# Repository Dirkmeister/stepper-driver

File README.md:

# Universal Stepper Tester

A bench tool for NEMA 17 and smaller bipolar stepper motors: plug a motor in, spin it, set current and microstepping, and read the driver's own diagnostics on an OLED. Every power-up runs a self test that names the failing part of the board. By -DK.

| | |
|---|---|
| MCU | ATmega328P (DIP-28, socketed), 16 MHz crystal, ISP-programmed, no bootloader |
| Driver | BigTreeTech TMC2209 V1.2 StepStick, single-wire UART, up to about 1.75 A RMS |
| UI | 0.96 in SSD1306 I2C OLED, EC11 encoder with push, on a separate front board |
| Power | 12 V brick, inline 2 A blade fuse, panel switch, reverse-polarity FET, L7805 |
| Boards | Rev A: main 100.6 x 89.0 mm + front 70.0 x 38.1 mm, 2 layers, one JLCPCB panel |
| Firmware | v1.0 (2026-10-12), no libraries, verified in a board simulator (sizes in `CLAUDE.md`) |

## Status

Rev A boards are built and the first one powers up; the motor only vibrates so far, and the real-hardware self test still has to be recorded. Details and open issues: **[STATUS.md](STATUS.md)**.

## Repository

| Path | What |
|---|---|
| [`STATUS.md`](STATUS.md) | current state, active thread, queue, open items |
| [`CHANGELOG.md`](CHANGELOG.md) | history |
| [`CLAUDE.md`](CLAUDE.md) | rules and session protocol for working on this with Claude |
| [`docs/hardware.md`](docs/hardware.md) | design reference: power path, pin map, connectors, BOM, layout rules, display options |
| [`docs/errata-rev-a.md`](docs/errata-rev-a.md) | known Rev A problems, workarounds, Rev B candidates |
| [`docs/assembly.md`](docs/assembly.md) | build order, first power-up, harnesses, ribbon, motor wiring |
| [`docs/firmware.md`](docs/firmware.md) | self test, controls, menu, faults, debug log, backlog |
| [`docs/build-and-flash.md`](docs/build-and-flash.md) | MiniCore, Uno as ISP, fuses, expected warnings |
| [`docs/decisions.md`](docs/decisions.md) | why the design is the way it is |
| [`docs/inventory.md`](docs/inventory.md) | parts the owner has stated outside his inventory file, and the buy list (the inventory file itself is in the claude.ai Project knowledge) |
| [`docs/history/`](docs/history/) | sources, the 2026-10-06 progress doc |
| [`docs/claude-project-instructions.md`](docs/claude-project-instructions.md) | text for the claude.ai Project's instructions field |
| [`docs/seeds.md`](docs/seeds.md) | opening message for the next thread |
| [`firmware/`](firmware/) | `stepper_tester/` (the board firmware), `bringup/` (old Uno breadboard sketches) |
| [`tools/`](tools/) | `build.sh` headless build, `sim/` board simulator with fault scenarios |
| [`hardware/`](hardware/) | Rev A KiCad project and production files, as ordered |

## Flash the firmware (short version)

1. Arduino IDE: add the MiniCore URL in Preferences, install **MiniCore** from Boards Manager.
2. Upload ArduinoISP to an Uno, then 10 uF from its RESET to GND.
3. Tools: MiniCore ATmega328, External 16 MHz, BOD 2.7V, EEPROM retained, LTO enabled, 328P / 328PA, No bootloader, Programmer "Arduino as ISP".
4. Wire the Uno to the chip (breadboard jig or J2), Burn Bootloader once per chip, then Sketch > Upload Using Programmer.

Full procedure and what the warnings mean: [`docs/build-and-flash.md`](docs/build-and-flash.md).

## Safety

- Never plug or unplug a motor with 12 V on.
- J1 pin 1 is **negative**.
- J3 (ISP PWR) off whenever the brick is plugged in.
- Keep the input at 9 to 14 V while the 15 V zener (D1) is fitted.

## Working on it

The repo is the source of truth. Work in small commits (`fw:`, `hw:`, `docs:`, `tools:`), keep `STATUS.md` current, tag firmware releases `fw-vX.Y` and ordered boards `hw-rev-X`. Firmware changes must pass `tools/build.sh` and `tools/sim/run_all.sh` before they go on a chip. Details in [`CLAUDE.md`](CLAUDE.md).

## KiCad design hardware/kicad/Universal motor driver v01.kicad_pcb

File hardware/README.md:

# Hardware design files

Rev A as ordered from JLCPCB, copied byte-for-byte from the owner's PC on 2026-11-25. Tag `hw-rev-a` marks the commit that added them. Where these files and `docs/hardware.md` (compiled from the design chats) disagree, the files win.

## What's here

| Path | What | Notes |
|---|---|---|
| `kicad/Universal motor driver v01.kicad_pro` | KiCad project | the project name has spaces |
| `kicad/Universal motor driver v01.kicad_sch` | root schematic, the only sheet | title block: Universal Stepper Tester, rev A, 2026-10-05 |
| `kicad/Universal motor driver v01.kicad_pcb` | the board as ordered | same file as KiCad's 2026-10-06 02:15 backup, saved between the two gerber exports below, which are identical |
| `kicad/stepper_tester.kicad_sym` | project symbol library | holds `BTT_TMC2209_V1.2` |
| `kicad/sym-lib-table` | project symbol library table | see Known issues |
| `production/rev-A/` | fab outputs from 2026-10-06 | see below |

## Production files (Rev A)

| File | Exported (2026-10-06, CDT) | Notes |
|---|---|---|
| `Universal_motor_driver_v01.zip` | 02:19 | gerbers and drills, the file JLC needs |
| `bom.csv`, `positions.csv`, `designators.csv`, `netlist.ipc` | 02:19 | same export; LCSC part numbers blank |
| `production.zip` | 02:13 | an earlier export of the same set |

Which zip was uploaded isn't recorded, and it doesn't matter: the two exports' gerbers and drills match line for line apart from the creation time. Both carry the two known export problems: the encoder slots are routed slots, not the G85 mode JLC asks for (errata E5), and the silkscreen has lines down to 0.064 mm (E6). A G85 drill file was exported at 02:18 but never went into a zip.

`.gitattributes` stores everything under `production/` exactly as exported (the csv and ipc files are CRLF).

## Known issues in these files

- `sym-lib-table` maps the `tmc2209 module` library to the project folder by an absolute path on the owner's PC, not to `stepper_tester.kicad_sym`, so it won't resolve in a clone. The schematic keeps its own copy of every symbol, so it opens anyway. For Rev B, point it at `${KIPRJMOD}/stepper_tester.kicad_sym`.
- Not committed, still on the owner's PC: KiCad backups, `.kicad_prl` (local window state), 7 older or unused `.kicad_sch` files, the loose 02:18 drill files and the `.csv` / `.xlsx` spreadsheets in the project folder.

## Revisions

| Rev | Date | Status | Notes |
|---|---|---|---|
| A | ordered by 2026-10-06, delivered 2026-10-12 | built, under test | errata in `docs/errata-rev-a.md` |
| B | | not started | candidate changes at the end of the errata doc |

From Rev B on: work on a branch (`hw/rev-b`), keep the KiCad project name, bump the silkscreen revision text, and tag `hw-rev-b` at the commit that gets ordered. Dallas creates tags (GitHub Releases or git on the PC): tag pushes from Claude sessions are refused.

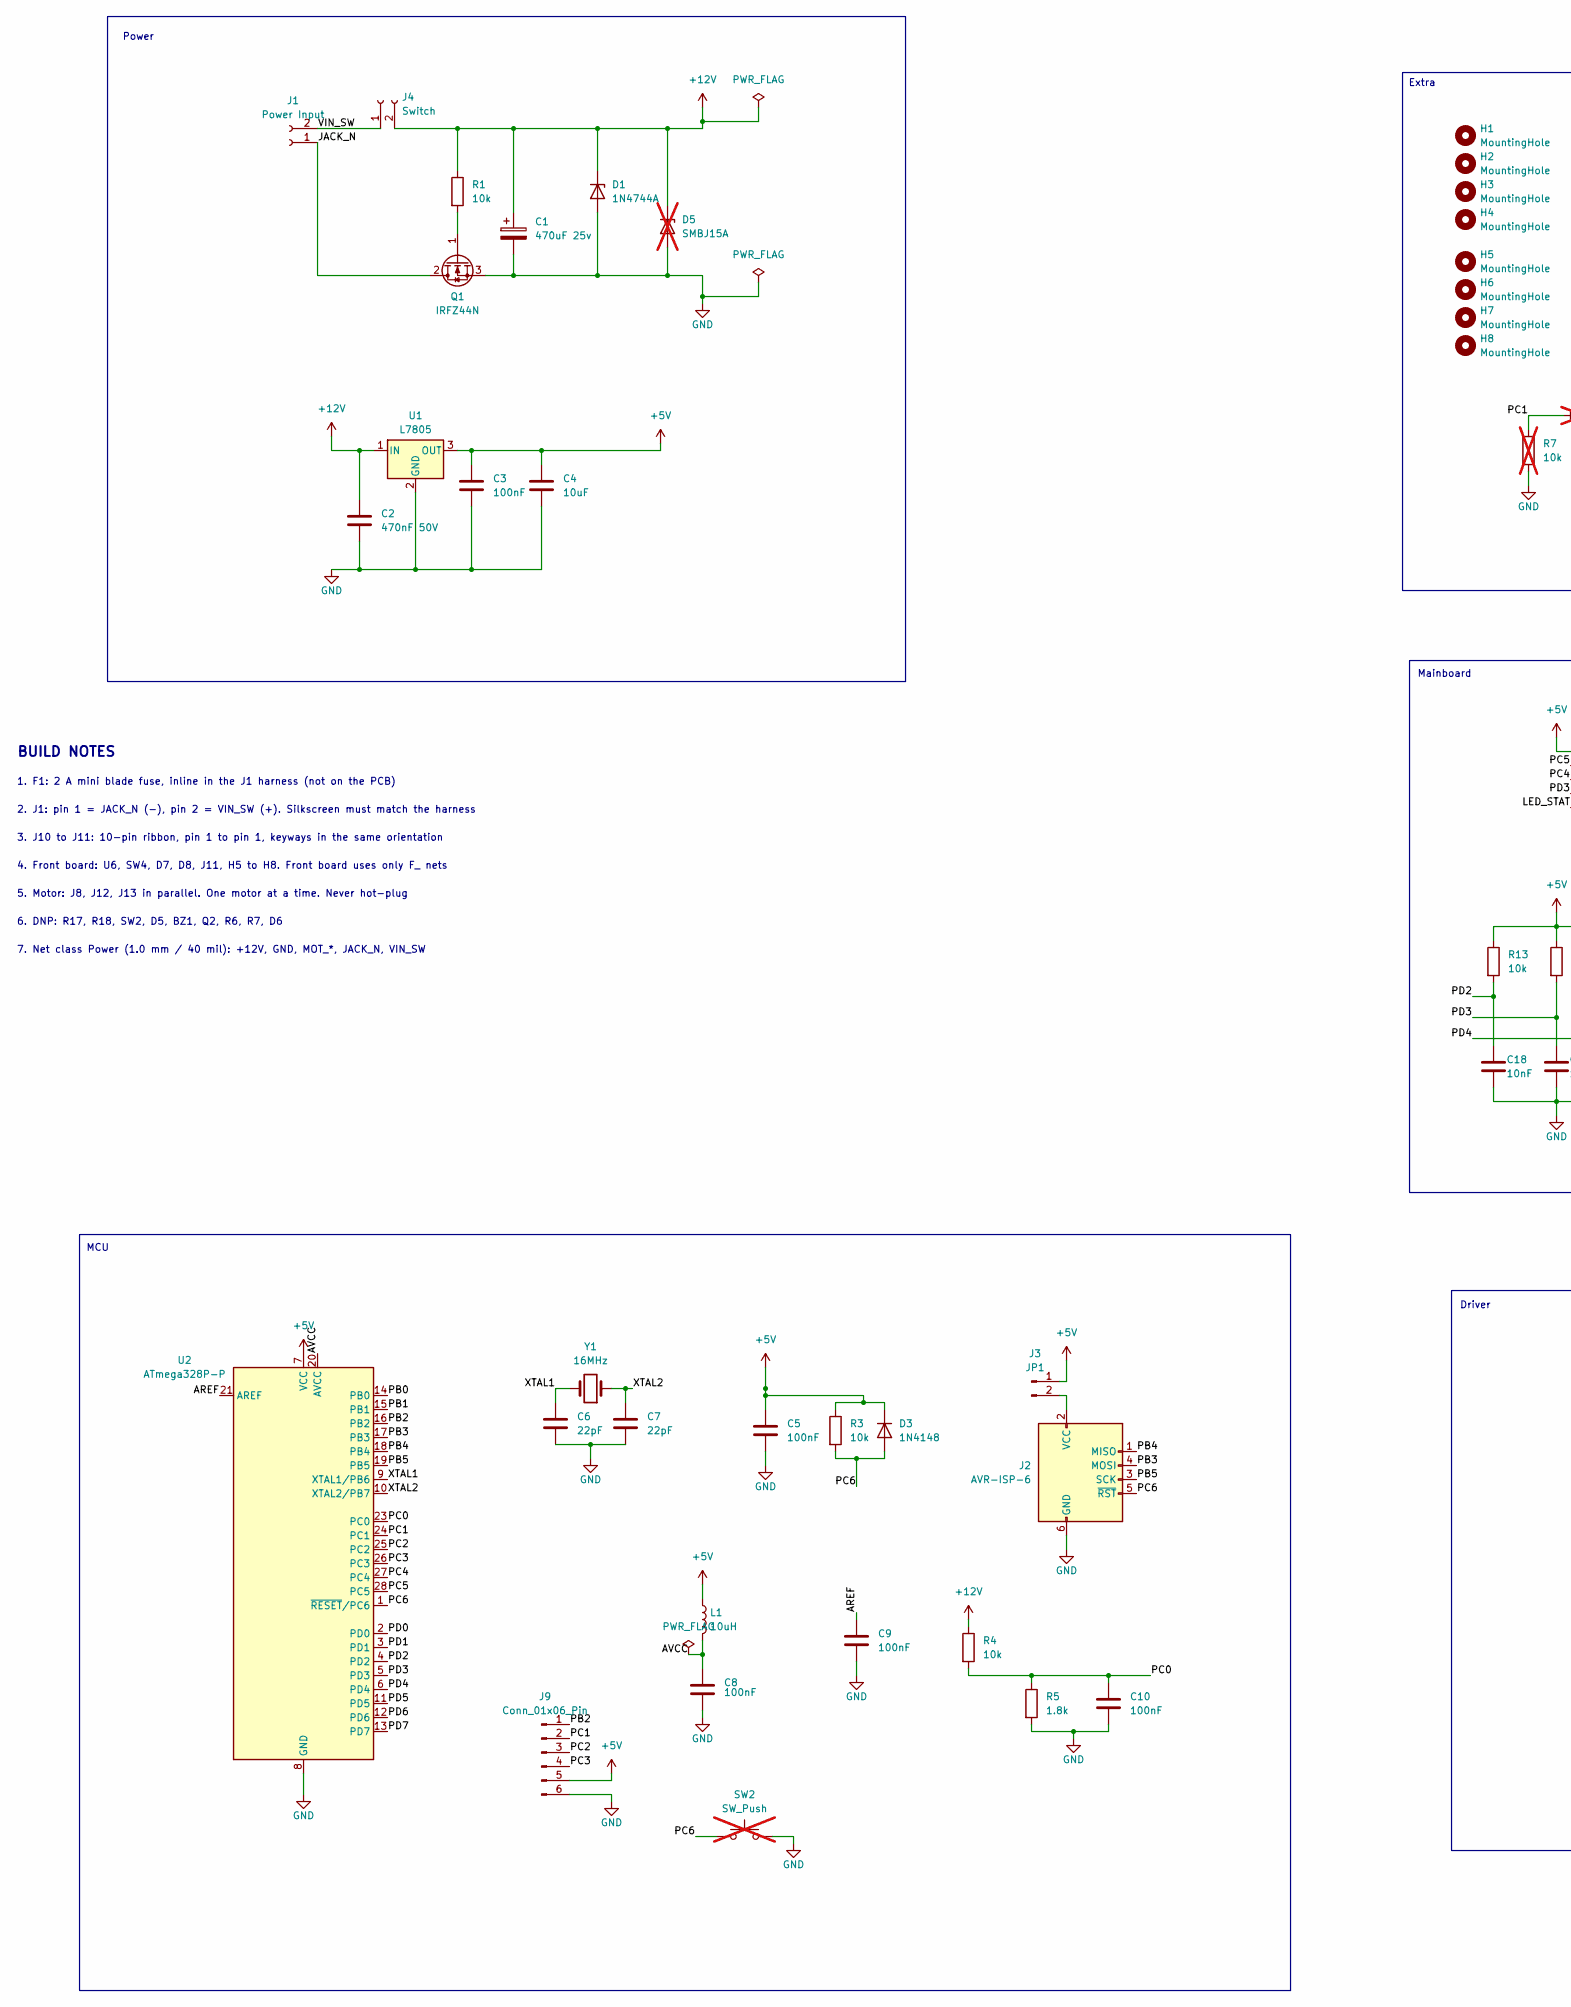
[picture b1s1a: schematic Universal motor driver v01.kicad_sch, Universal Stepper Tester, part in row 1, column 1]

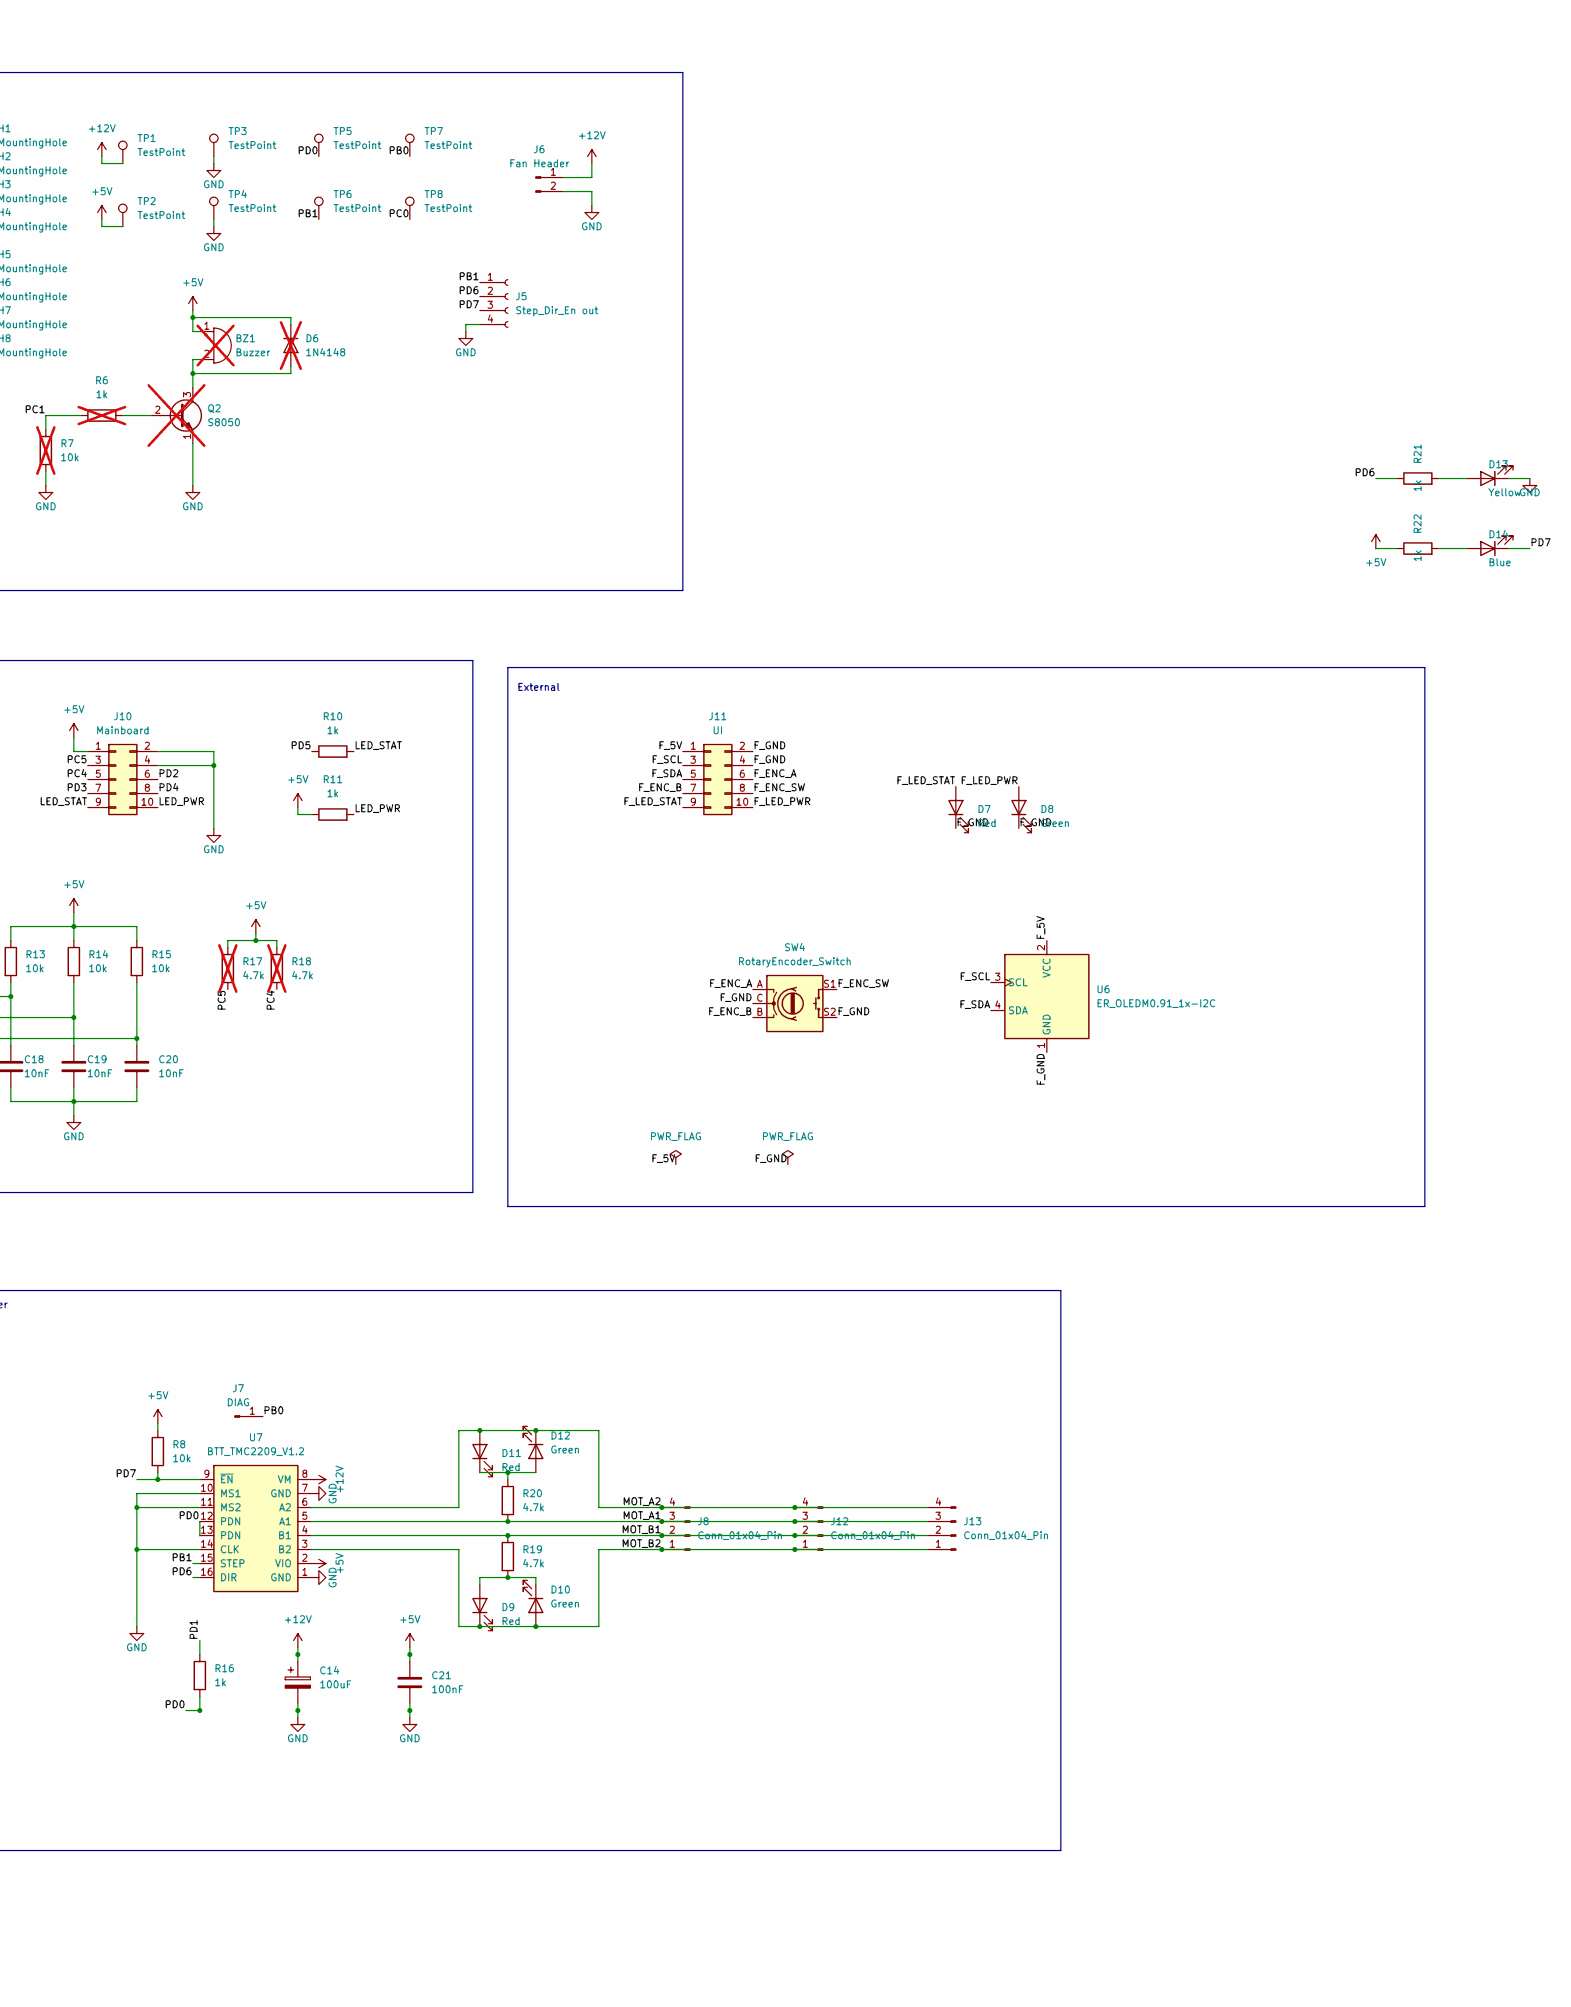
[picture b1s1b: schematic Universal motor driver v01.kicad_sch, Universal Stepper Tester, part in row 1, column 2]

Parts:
BZ1: Buzzer; Buzzer_12x9.5RM7.6; not fitted
C1: 470uF 25v; CP_Radial_D10.0mm_P5.00mm
C2: 470nF 50V; C_0805_2012Metric_Pad1.18x1.45mm_HandSolder
C3, C5, C8, C9, C10, C21: 100nF; C_0805_2012Metric_Pad1.18x1.45mm_HandSolder
C4: 10uF; C_0805_2012Metric_Pad1.18x1.45mm_HandSolder
C6, C7: 22pF; C_0805_2012Metric_Pad1.18x1.45mm_HandSolder
C14: 100uF; CP_Radial_D6.3mm_P2.50mm
C18, C19, C20: 10nF; C_0805_2012Metric_Pad1.18x1.45mm_HandSolder
D1: 1N4744A; D_DO-41_SOD81_P10.16mm_Horizontal
D3: 1N4148; D_DO-35_SOD27_P7.62mm_Horizontal
D5: SMBJ15A; D_SMB; not fitted
D6: 1N4148; D_DO-35_SOD27_P7.62mm_Horizontal; not fitted
D7: Red; LED_D5.0mm
D8: Green; LED_D5.0mm
D9, D11: Red; LED_0805_2012Metric_Pad1.15x1.40mm_HandSolder
D10, D12: Green; LED_0805_2012Metric_Pad1.15x1.40mm_HandSolder
D13: Yellow; LED_0805_2012Metric_Pad1.15x1.40mm_HandSolder
D14: Blue; LED_0805_2012Metric_Pad1.15x1.40mm_HandSolder
H1, H2, H3, H4, H5, H6, H7, H8: MountingHole; MountingHole_3.2mm_M3_ISO14580
J1: Power Input; JST_XH_B2B-XH-A_1x02_P2.50mm_Vertical
J2: AVR-ISP-6; IDC-Header_2x03_P2.54mm_Vertical
J3: JP1; PinHeader_1x02_P2.54mm_Vertical
J4: Switch; JST_XH_B2B-XH-A_1x02_P2.50mm_Vertical
J5: Step_Dir_En out; JST_XH_B4B-XH-A_1x04_P2.50mm_Vertical
J6: Fan Header; JST_XH_B2B-XH-A_1x02_P2.50mm_Vertical
J7: DIAG; PinHeader_1x01_P2.54mm_Vertical
J8: Conn_01x04_Pin; JST_XH_B4B-XH-AM_1x04_P2.50mm_Vertical
J9: Conn_01x06_Pin; PinHeader_1x06_P2.54mm_Vertical
J10: Mainboard; IDC-Header_2x05_P2.54mm_Vertical
J11: UI; IDC-Header_2x05_P2.54mm_Vertical
J12: Conn_01x04_Pin; PinHeader_1x04_P2.54mm_Vertical
J13: Conn_01x04_Pin; TerminalBlock_Phoenix_MKDS-1,5-4-5.08_1x04_P5.08mm_Horizont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
L1: 10uH; R_0805_2012Metric_Pad1.20x1.40mm_HandSolder
Q1: IRFZ44N; TO-220-3_Vertical
Q2: S8050; TO-92_Inline; not fitted
R1, R3, R4, R8, R13, R14, R15: 10k; R_0805_2012Metric_Pad1.20x1.40mm_HandSolder
R5: 1.8k; R_0805_2012Metric_Pad1.20x1.40mm_HandSolder
R6: 1k; R_0805_2012Metric_Pad1.20x1.40mm_HandSolder; not fitted
R7: 10k; R_0805_2012Metric_Pad1.20x1.40mm_HandSolder; not fitted
R10, R11, R16, R21, R22: 1k; R_0805_2012Metric_Pad1.20x1.40mm_HandSolder
R17, R18: 4.7k; R_0805_2012Metric_Pad1.20x1.40mm_HandSolder; not fitted
R19, R20: 4.7k; R_0805_2012Metric_Pad1.20x1.40mm_HandSolder
SW2: SW_Push; SW_PUSH_6mm; not fitted
SW4: RotaryEncoder_Switch; RotaryEncoder_Alps_EC11E-Switch_Vertical_H20mm
TP1, TP2, TP3, TP4, TP5, TP6, TP7, TP8: TestPoint; TestPoint_Keystone_5000-5004_Miniature
U1: L7805; TO-220-3_Vertical
U2: ATmega328P-P; DIP-28_W7.62mm
U6: ER_OLEDM0.91_1x-I2C; PinHeader_1x04_P2.54mm_Vertical
U7: BTT_TMC2209_V1.2; Pololu_Breakout-16_15.2x20.3mm
Y1: 16MHz; Crystal_HC49-4H_Vertical

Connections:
+5V: BZ1.1 (+), C3.1, C4.1, C5.1, C21.1, D3.1 (K), D6.1 (K), J3.1, J9.5, J10.1, L1.1, R3.1, R8.1, R11.1, R13.1, R14.1, R15.1, R17.1, R18.1, R22.1, TP2.1 (1_1), U1.3 (OUT), U2.7 (VCC), U7.2 (VIO)
+12V: C1.1, C2.1, C14.1, D1.1 (K), D5.1 (K), J4.2, J6.1, R1.1, R4.1, TP1.1 (1_1), U1.1 (IN), U7.8 (VM)
/AREF: C9.1, U2.21 (AREF)
/AVCC: C8.1, L1.2, U2.20 (AVCC)
/F_5V: J11.1, U6.2 (VCC)
/F_ENC_A: J11.6, SW4.A
/F_ENC_B: J11.7, SW4.B
/F_ENC_SW: J11.8, SW4.S1
/F_GND: D7.1 (K), D8.1 (K), J11.2, J11.4, SW4.C, SW4.S2, U6.1 (GND)
/F_LED_PWR: D8.2 (A), J11.10
/F_LED_STAT: D7.2 (A), J11.9
/F_SCL: J11.3, U6.3 (SCL)
/F_SDA: J11.5, U6.4 (SDA)
/JACK_N: J1.1, Q1.2 (D)
/LED_PWR: J10.10, R11.2
/LED_STAT: J10.9, R10.2
/MOT_A1: J8.3, J12.3, J13.3, R20.2, U7.5 (A1)
/MOT_A2: D11.2 (A), D12.1 (K), J8.4, J12.4, J13.4, U7.6 (A2)
/MOT_B1: J8.2, J12.2, J13.2, R19.1, U7.4 (B1)
/MOT_B2: D9.1 (K), D10.2 (A), J8.1, J12.1, J13.1, U7.3 (B2)
/PB0: J7.1 (Pin_1_1), TP7.1 (1_1), U2.14 (PB0)
/PB1: J5.1, TP6.1 (1_1), U2.15 (PB1), U7.15 (STEP)
/PB2: J9.1, U2.16 (PB2)
/PB3: J2.4 (MOSI), U2.17 (PB3)
/PB4: J2.1 (MISO), U2.18 (PB4)
/PB5: J2.3 (SCK), U2.19 (PB5)
/PC0: C10.1, R4.2, R5.1, TP8.1 (1_1), U2.23 (PC0)
/PC1: J9.2, R6.1, R7.1, U2.24 (PC1)
/PC2: J9.3, U2.25 (PC2)
/PC3: J9.4, U2.26 (PC3)
/PC4: J10.5, R18.2, U2.27 (PC4)
/PC5: J10.3, R17.2, U2.28 (PC5)
/PC6: D3.2 (A), J2.5 (~RST), R3.2, SW2.1, U2.1 (~RESET/PC6)
/PD0: R16.2, TP5.1 (1_1), U2.2 (PD0), U7.12 (PDN), U7.13 (PDN)
/PD1: R16.1, U2.3 (PD1)
/PD2: C18.1, J10.6, R13.2, U2.4 (PD2)
/PD3: C19.1, J10.7, R14.2, U2.5 (PD3)
/PD4: C20.1, J10.8, R15.2, U2.6 (PD4)
/PD5: R10.1, U2.11 (PD5)
/PD6: J5.2, R21.1, U2.12 (PD6), U7.16 (DIR)
/PD7: D14.1 (K), J5.3, R8.2, U2.13 (PD7), U7.9 (~EN)
/VIN_SW: J1.2, J4.1
/XTAL1: C6.1, U2.9 (XTAL1/PB6), Y1.2
/XTAL2: C7.1, U2.10 (XTAL2/PB7), Y1.1
GND: C1.2, C2.2, C3.2, C4.2, C5.2, C6.2, C7.2, C8.2, C9.2, C10.2, C14.2, C18.2, C19.2, C20.2, C21.2, D1.2 (A), D5.2 (A), D13.1 (K), J2.6 (GND), J5.4, J6.2, J9.6, J10.2, J10.4, Q1.3 (S), Q2.1 (E), R5.2, R7.2, SW2.2, TP3.1 (1_1), TP4.1 (1_1), U1.2 (GND), U2.8 (GND), U2.22 (GND), U7.1 (GND), U7.7 (GND), U7.10 (MS1), U7.11 (MS2), U7.14 (CLK)
unnamed: BZ1.2 (-), D6.2 (A), Q2.3 (C)
unnamed: D9.2 (A), D10.1 (K), R19.2
unnamed: D11.1 (K), D12.2 (A), R20.1
unnamed: D13.2 (A), R21.2
unnamed: D14.2 (A), R22.2
unnamed: J2.2 (VCC), J3.2
unnamed: Q1.1 (G), R1.2
unnamed: Q2.2 (B), R6.2

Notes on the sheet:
Driver
Mainboard
MCU
External
Extra
Power
BUILD NOTES
1. F1: 2 A mini blade fuse, inline in the J1 harness (not on the PCB)
2. J1: pin 1 = JACK_N (-), pin 2 = VIN_SW (+). Silkscreen must match the harness
3. J10 to J11: 10-pin ribbon, pin 1 to pin 1, keyways in the same orientation
4. Front board: U6, SW4, D7, D8, J11, H5 to H8. Front board uses only F_ nets
5. Motor: J8, J12, J13 in parallel. One motor at a time. Never hot-plug
6. DNP: R17, R18, SW2, D5, BZ1, Q2, R6, R7, D6
7. Net class Power (1.0 mm / 40 mil): +12V, GND, MOT_*, JACK_N, VIN_SW

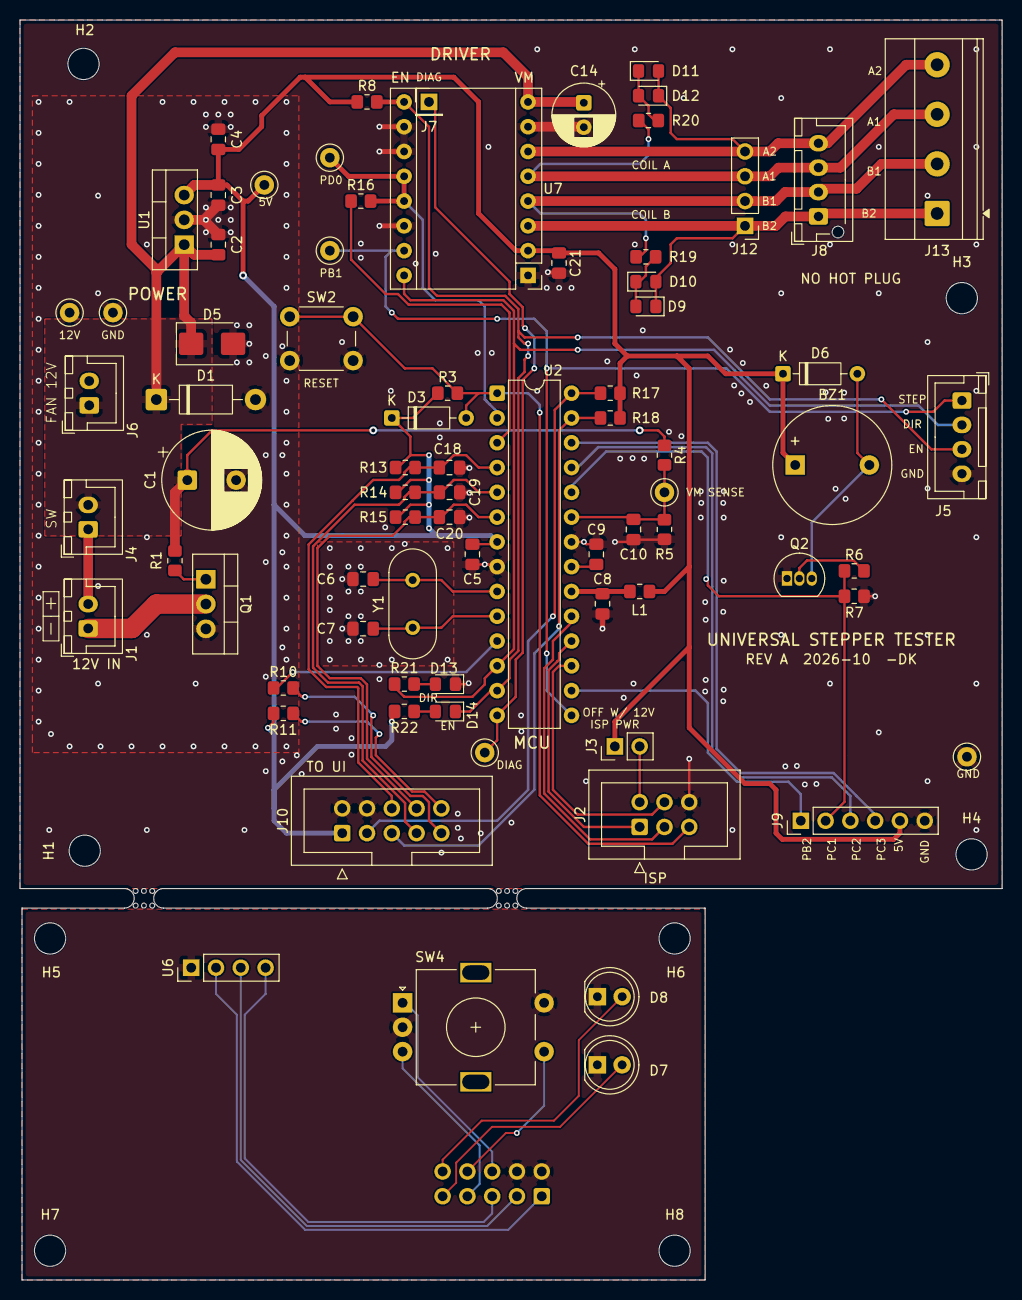
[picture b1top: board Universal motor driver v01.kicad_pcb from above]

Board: 2 copper layers, 100.6 x 129.1 mm, 86 parts (1 on the bottom side), 53 nets.

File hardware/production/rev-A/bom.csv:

Designator,Footprint,Quantity,Value,LCSC Part #
BZ1,Buzzer_12x9.5RM7.6,1,Buzzer,
C1,CP_Radial_D10.0mm_P5.00mm,1,470uF 25v,
"C10, C21, C3, C5, C8, C9",0805,6,100nF,
C14,CP_Radial_D6.3mm_P2.50mm,1,100uF,
"C18, C19, C20",0805,3,10nF,
C2,0805,1,470nF 50V,
C4,0805,1,10uF,
"C6, C7",0805,2,22pF,
D1,D_DO-41_SOD81_P10.16mm_Horizontal,1,1N4744A,
"D10, D12",0805,2,Green,
"D11, D9",0805,2,Red,
D13,0805,1,Yellow,
D14,0805,1,Blue,
"D3, D6",D_DO-35_SOD27_P7.62mm_Horizontal,2,1N4148,
D5,D_SMB,1,SMBJ15A,
D7,LED_D5.0mm,1,Red,
D8,LED_D5.0mm,1,Green,
J1,JST_XH_B2B-XH-A_1x02_P2.50mm_Vertical,1,Power Input,
J10,IDC-Header_2x05_P2.54mm_Vertical,1,Mainboard,
J11,IDC-Header_2x05_P2.54mm_Vertical,1,UI,
J12,PinHeader_1x04_P2.54mm_Vertical,1,Conn_01x04_Pin,
J13,"TerminalBlock_Phoenix_MKDS-1,5-4-5.08_1x04_P5.08mm_Horizontal",1,Conn_01x04_Pin,
J2,IDC-Header_2x03_P2.54mm_Vertical,1,AVR-ISP-6,
J3,PinHeader_1x02_P2.54mm_Vertical,1,JP1,
J4,JST_XH_B2B-XH-A_1x02_P2.50mm_Vertical,1,Switch,
J5,JST_XH_B4B-XH-A_1x04_P2.50mm_Vertical,1,Step_Dir_En out,
J6,JST_XH_B2B-XH-A_1x02_P2.50mm_Vertical,1,Fan Header,
J7,PinHeader_1x01_P2.54mm_Vertical,1,DIAG,
J8,JST_XH_B4B-XH-AM_1x04_P2.50mm_Vertical,1,Conn_01x04_Pin,
J9,PinHeader_1x06_P2.54mm_Vertical,1,Conn_01x06_Pin,
L1,0805,1,10uH,
Q1,TO-220-3_Vertical,1,IRFZ44N,
Q2,TO-92_Inline,1,S8050,
"R1, R13, R14, R15, R3, R4, R7, R8",0805,8,10k,
"R10, R11, R16, R21, R22, R6",0805,6,1k,
"R17, R18, R19, R20",0805,4,4.7k,
R5,0805,1,1.8k,
SW2,SW_PUSH_6mm,1,SW_Push,
SW4,RotaryEncoder_Alps_EC11E-Switch_Vertical_H20mm,1,RotaryEncoder_Switch,
"TP1, TP2, TP3, TP4, TP5, TP6, TP7, TP8",TestPoint_Keystone_5000-5004_Miniature,8,TestPoint,
U1,TO-220-3_Vertical,1,L7805,
U2,DIP-28_W7.62mm,1,ATmega328P-P,
U6,PinHeader_1x04_P2.54mm_Vertical,1,ER_OLEDM0.91_1x-I2C,
U7,Pololu_Breakout-16_15.2x20.3mm,1,BTT_TMC2209_V1.2,
Y1,Crystal_HC49-4H_Vertical,1,16MHz,

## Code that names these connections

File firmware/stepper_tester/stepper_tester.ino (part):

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   ======================================================================
   Board   : Universal_motor_driver_v09 main board + front UI board
   MCU     : ATmega328P, 16 MHz crystal, programmed over ISP, no bootloader
   Driver  : BTT TMC2209 V1.2, UART on PD0/PD1 (R16 1k on TX), address 0
   Display : SSD1306 128x64 I2C OLED over the J10/J11 ribbon
   Libraries: none. The OLED, I2C and TMC2209 UART code are all built in,
             so the self test can say exactly where a fault is and nothing
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      3 VM    motor supply through the 10k / 1.8k divider
      4 OLED  SDA/SCL idle high, ACK at 0x3C or 0x3D, 400 kHz then 100 kHz
      5 KNOB  button released
      6 UART  echo through R16: proves PD1, R16, PD0 and the PDN net
      7 LINK  driver answers (scans addresses 1-3 if not at 0)
      8 DRV   version 0x21, IFCNT counts every write, config reads back
      9 PINS  EN, DIR, STEP toggled and read back through IOIN
     10 DIAG  PB0 pulled up, driver holds it low: wired or not (optional)
     11 OUT   outputs on at 306 mA for 80 ms, short-to-GND / supply latches
   Tests 7-11 need 12 V on VM. A self test that ran without it re-runs by
   itself once VM shows up.
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     on               motor running
     fast flicker     fault (press the knob to clear)

   Debug log (optional): J9 pin 1 (PB2) to a USB-serial RX, J9 pin 6 GND,
   57600 8N1. No adapter? A Nano with RESET jumpered to GND works: PB2 to
   the Nano's TX pin (D1), GNDs together, Serial Monitor on the Nano's port.
   ====================================================================== */

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#define FW_VER "1.0"

// ---------------------------------------------------------------- pins
// PORTD: PD0 RXD + PD1 TXD (driver UART), PD2 ENC_A, PD3 ENC_B, PD4 ENC_SW,
//        PD5 status LED, PD6 DIR, PD7 EN
// PORTB: PB0 DIAG (J7), PB1 STEP (OC1A), PB2 debug TX (J9-1), PB3..5 ISP only
// PORTC: PC0 VM sense (10k/1.8k), PC1 buzzer (DNP), PC2/PC3 spare (J9),
//        PC4 SDA, PC5 SCL
#define EN_OFF()   (PORTD |=  _BV(PD7))   // high = driver off (R8 holds this during reset)
#define EN_ON()    (PORTD &= ~_BV(PD7))   // low  = driver on, blue EN LED (D14) lights
#define DIR_HI()   (PORTD |=  _BV(PD6))
#define DIR_LO()   (PORTD &= ~_BV(PD6))
#define LED_ON()   (PORTD |=  _BV(PD5))
#define LED_OFF()  (PORTD &= ~_BV(PD5))
#define SW_DOWN()  (!(PIND & _BV(PD4)))
#define DIAG_HI()  (PINB & _BV(PB0))

// ---------------------------------------------------------------- limits
#define VM_ABSENT_MV  4000    // below this: no motor supply at all
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static uint8_t  tmcAddr;            // UART address in use (0 unless MS1/MS2 are wrong)
static bool     tmcOk;              // link up and configured
static bool     spreadPin;          // SPREAD pin level seen in IOIN (inverts en_SpreadCycle)
static bool     diagWired;          // DIAG reaches PB0
static uint8_t  echoState;          // last UART echo: 0 ok, 1 none, 2 garbled, 3 line low
static uint8_t  gCS, gVs;           // current scale and vsense for S.mA
static uint32_t drvStatus;
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static uint8_t  fault;
static uint8_t  sgLowCount;

// STEP timer (Timer1, OC1A = PB1)
static volatile uint16_t t1Top, t1Ocr;
static volatile uint8_t  t1Cs, t1Pend;
static uint8_t  stepOn;
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void dbgTx(uint8_t c) {
  uint8_t s = SREG;
  cli();
  PORTB &= ~_BV(PB2);                                   // start bit
  __builtin_avr_delay_cycles(DBG_CYC - 7);
  for (uint8_t i = 0; i < 8; i++) {
    if (c & 1) PORTB |= _BV(PB2); else PORTB &= ~_BV(PB2);
    c >>= 1;
    __builtin_avr_delay_cycles(DBG_CYC - 13);
  }
  __builtin_avr_delay_cycles(6);
  PORTB |= _BV(PB2);                                    // stop bit
  SREG = s;
  __builtin_avr_delay_cycles(DBG_CYC);
}
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// bounce or a missed edge can never leave it half a click off.
static const int8_t QEM[16] PROGMEM = {0, -1, 1, 0, 1, 0, 0, -1, -1, 0, 0, 1, 0, 1, -1, 0};
ISR(INT0_vect) {
  uint8_t s = (PIND >> PD2) & 3;                       // bit0 = A (PD2), bit1 = B (PD3)
  encAcc += (int8_t)pgm_read_byte(&QEM[(encPrev << 2) | s]);
  encPrev = s;
  if (s == encRest) {
    int8_t d = encAcc <= -2 ? 1 : (encAcc >= 2 ? -1 : 0);   // A on PD2: clockwise counts negative
    encDet += d;
    if (d && btnDown) btnTurned = 1;
    encAcc = 0;
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  TCCR2B = _BV(CS22);
  OCR2A = 249;
  TIMSK2 = _BV(OCIE2A);
  encPrev = encRest = (PIND >> PD2) & 3;              // the knob sits in a detent at power-up
  EICRA = _BV(ISC00) | _BV(ISC10);                     // any edge on INT0 and INT1
  EIFR = 3;
  EIMSK = _BV(INT0) | _BV(INT1);
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// request's sync byte and answers at that rate, so the +2 % offset from
// 115,200 does not matter.
void uartInit() {
  PORTD |= _BV(PD0);                                   // pull-up: an open RX idles high
  UBRR0 = 16;
  UCSR0A = _BV(U2X0);
  UCSR0C = _BV(UCSZ01) | _BV(UCSZ00);
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  return m < MAX_CRPM ? m : MAX_CRPM;
}

// ================================================================ STEP pulses (Timer1 -> OC1A = PB1)
// Fast PWM mode 14 (TOP = ICR1), ~4 us high pulses. ICR1 is not double
// buffered, so speed changes are applied in the overflow interrupt, right
// after the counter wraps.
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void stepStop() {
  TIMSK1 = 0;
  TCCR1B = 0;
  TCCR1A = 0;                                          // PB1 back to PORTB, which is low
  PORTB &= ~_BV(PB1);
  stepOn = 0;
}

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
void testOled() {
  // Both lines must idle high (R17/R18 4.7k + module pull-ups + internal).
  DDRC &= ~(_BV(PC4) | _BV(PC5));
  PORTC |= _BV(PC4) | _BV(PC5);
  _delay_us(50);
  if ((PINC & _BV(PC5)) && !(PINC & _BV(PC4))) {       // SDA held by a slave: clock it free
    for (uint8_t i = 0; i < 9; i++) {
      DDRC |= _BV(PC5); _delay_us(10);
      DDRC &= ~_BV(PC5); _delay_us(10);
    }
  }
  uint8_t lines = PINC & (_BV(PC4) | _BV(PC5));
  if (lines != (_BV(PC4) | _BV(PC5))) {
    setRes(T_OLED, R_FAIL, 1, (lines & _BV(PC4) ? 0 : 1) | (lines & _BV(PC5) ? 0 : 2));
    return;
  }
  for (oledFast = 1; ; oledFast = 0) {                 // 400 kHz first, then 100 kHz
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  // toff = 0 first, so EN low cannot energize anything.
  tmcWrite(R_CHOPCONF, chopVal(S.mres, 0));
  uint32_t a = 0, b = 0;
  EN_OFF(); DIR_LO(); PORTB &= ~_BV(PB1); delay(1);
  bool r1 = tmcRead(R_IOIN, &a) == TE_OK;
  EN_ON(); DIR_HI(); PORTB |= _BV(PB1); delay(1);
  bool r2 = tmcRead(R_IOIN, &b) == TE_OK;
  EN_OFF(); DIR_LO(); PORTB &= ~_BV(PB1);
  if (!r1 || !r2) setRes(T_PINS, R_FAIL, 8, 0);
  else {
    uint8_t bad = 0;
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  }
  tmcWrite(R_CHOPCONF, chopVal(S.mres, 3));

  // T_DIAG: with EN high the driver holds DIAG low. PB0 has its pull-up on,
  // so reading high means nothing drives it (module pin not wired to J7).
  delay(2);
  bool pinHi = DIAG_HI();
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  wdt_reset();

  // 5. Knob button must be released by now
  setRes(T_KNOB, SW_DOWN() ? R_FAIL : R_OK, SW_DOWN() ? 1 : 0, (PIND >> PD2) & 7);

  // 6..11. Driver
  testDriver();
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      case T_LINK: return PSTR("Driver answers\nat address 0");
      case T_DRV:  return PSTR("Version 0x21, writes\ncounted, readback ok");
      case T_PINS: return PSTR("Driver sees EN, DIR\nand STEP toggle");
      case T_DIAG: return PSTR("DIAG reaches PB0");
      case T_OUT:  return PSTR("Outputs on, no short\n(coil LEDs flashed)");
    }
  }
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                 if (c == 3) return PSTR("Only works at 100k.\nRibbon/pull-ups weak");
                 return PSTR("No ACK: check ribbon\nJ10/J11, U6 solder");
    case T_KNOB: return PSTR("Button stuck low.\nSW4 / ENC_SW short");
    case T_UART: if (c == 1) return PSTR("No echo. Check R16,\nPD0/PD1 traces");
                 if (c == 2) return PSTR("Echo garbled. Line\ncontention on PDN");
                 return PSTR("PDN line held low.\nShort on UART net");
    case T_LINK: if (c == 2) return PSTR("Driver on wrong addr\nMS1/MS2 not to GND");
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// ================================================================ setup / loop
void setup() {
  // Outputs to a safe state first: driver off, no step pulses, LED on
  PORTD = _BV(PD7) | _BV(PD5) | _BV(PD4) | _BV(PD3) | _BV(PD2);  // EN high, LED on, knob pull-ups
  DDRD  = _BV(PD7) | _BV(PD6) | _BV(PD5);
  PORTB = _BV(PB2) | _BV(PB0) | _BV(PB3) | _BV(PB4) | _BV(PB5);  // debug idle high, DIAG + unused pulled up
  DDRB  = _BV(PB1) | _BV(PB2);
  PORTC = _BV(PC2) | _BV(PC3);                                   // spare J9 pins pulled up
  DDRC  = _BV(PC1);                                              // buzzer transistor off
  DIDR0 = _BV(ADC0D);                                            // VM sense pin: analog only
  uartInit();

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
